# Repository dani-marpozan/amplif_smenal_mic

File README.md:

# Amplificator de semnal mic cu tranzistor bipolar

Model 3D

## Schematic

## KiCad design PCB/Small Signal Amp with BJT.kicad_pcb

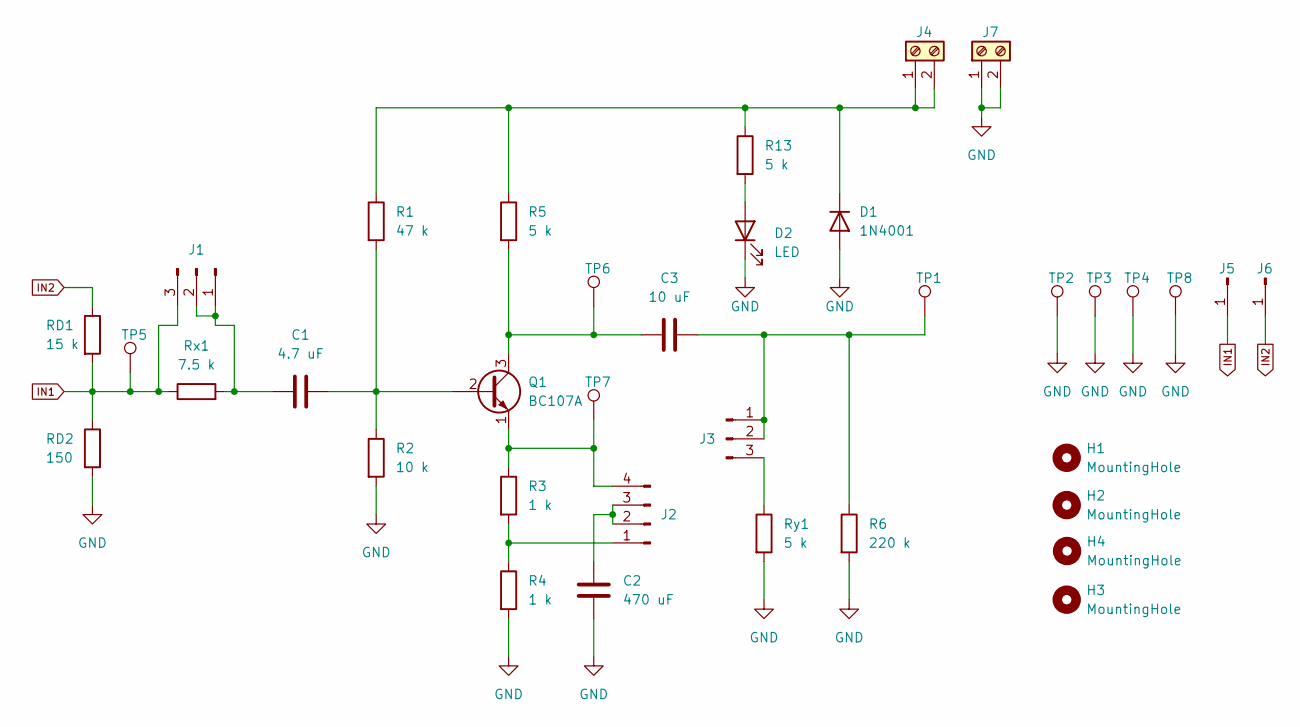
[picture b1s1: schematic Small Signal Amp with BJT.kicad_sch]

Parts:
C1: 4.7 uF; CP_Radial_D5.0mm_P2.00mm
C2: 470 uF; CP_Radial_D8.0mm_P3.50mm
C3: 10 uF; CP_Radial_D5.0mm_P2.00mm
D1: 1N4001; D_DO-41_SOD81_P10.16mm_Horizontal
D2: LED; LED_D3.0mm
H1, H2, H3, H4: MountingHole; MountingHole_3.2mm_M3_ISO7380_Pad_TopBottom
J1, J3: Conn_01x03_Male; PinHeader_1x03_P2.54mm_Vertical
J2: Conn_01x04_Male; PinHeader_1x04_P2.54mm_Vertical
J4, J7: Screw_Terminal_01x02; TerminalBlock_Phoenix_MKDS-1,5-2_1x02_P5.00mm_Horizontal
J5, J6: Conn_01x01_Male; TestPoint
Q1: BC107A; TO-18-3
R1: 47 k; R_Axial_DIN0207_L6.3mm_D2.5mm_P10.16mm_Horizontal
R2: 10 k; R_Axial_DIN0207_L6.3mm_D2.5mm_P10.16mm_Horizontal
R3, R4: 1 k; R_Axial_DIN0207_L6.3mm_D2.5mm_P10.16mm_Horizontal
R5, R13: 5 k; R_Axial_DIN0207_L6.3mm_D2.5mm_P10.16mm_Horizontal
R6: 220 k; R_Axial_DIN0207_L6.3mm_D2.5mm_P10.16mm_Horizontal
RD1: 15 k; R_Axial_DIN0207_L6.3mm_D2.5mm_P10.16mm_Horizontal
RD2: 150; R_Axial_DIN0207_L6.3mm_D2.5mm_P10.16mm_Horizontal
Rx1: 7.5 k; R_Axial_DIN0207_L6.3mm_D2.5mm_P10.16mm_Horizontal
Ry1: 5 k; R_Axial_DIN0207_L6.3mm_D2.5mm_P10.16mm_Horizontal
TP1, TP5, TP6, TP7: TestPoint; Kesytone TP Multipurpose 5013
TP2, TP3, TP4, TP8: TestPoint

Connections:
GND: C2.2, D1.2 (A), D2.1 (K), J7.1, J7.2, R2.2, R4.2, R6.2, RD2.2, Ry1.2, TP2.1, TP3.1, TP4.1, TP8.1
IN1: J1.3, J5.1, RD1.2, RD2.1, Rx1.1, TP5.1
IN2: J6.1, RD1.1
unnamed: D1.1 (K), J4.1, J4.2, R1.1, R5.1, R13.1
unnamed: D2.2 (A), R13.2
unnamed: C1.2, J1.1, J1.2, Rx1.2
unnamed: J2.1, R3.2, R4.1
unnamed: C2.1, J2.2, J2.3
unnamed: J2.4, Q1.1 (E), R3.1, TP7.1
unnamed: C3.2, J3.1, J3.2, R6.1, TP1.1
unnamed: J3.3, Ry1.1
unnamed: C1.1, Q1.2 (B), R1.2, R2.1
unnamed: C3.1, Q1.3 (C), R5.2, TP6.1

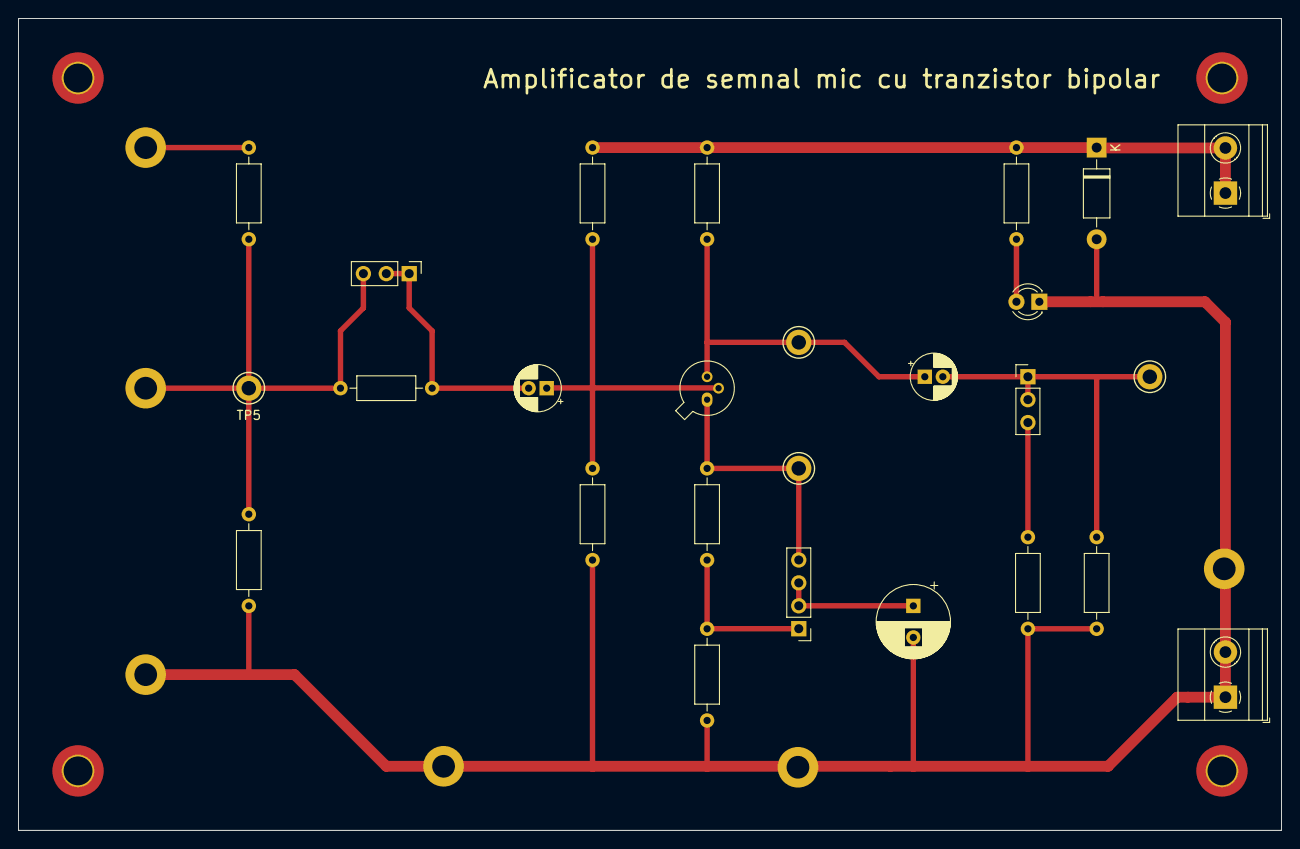
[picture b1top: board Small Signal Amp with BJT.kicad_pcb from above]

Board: 2 copper layers, 140.0 x 90.0 mm, 36 parts (0 on the bottom side), 13 nets.
